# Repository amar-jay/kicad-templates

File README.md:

# KiCad Templates

> [!NOTE]
>	This is a fork of the original [KiCad Templates repository](https://gitlab.com/kicad/libraries/kicad-templates) to provide updated templates for KiCad 9.0 and later versions.
> This fork includes templates designed for specific manufacturers, usecases and inmproved aesthetics.
> It is personally maintained by [amar-jay](https://github.com/amar-jay). 

This repository contains the official KiCad project and worksheet templates.

Contribution guidelines can be found at http://kicad.org/libraries/contribute
The library convention can be found at http://kicad.org/libraries/klc/

Other KiCad library repositories are located:

* Symbols: https://gitlab.com/kicad/libraries/kicad-symbols
* Footprints: https://gitlab.com/kicad/libraries/kicad-footprints
* 3D Models: https://gitlab.com/kicad/libraries/kicad-packages3d

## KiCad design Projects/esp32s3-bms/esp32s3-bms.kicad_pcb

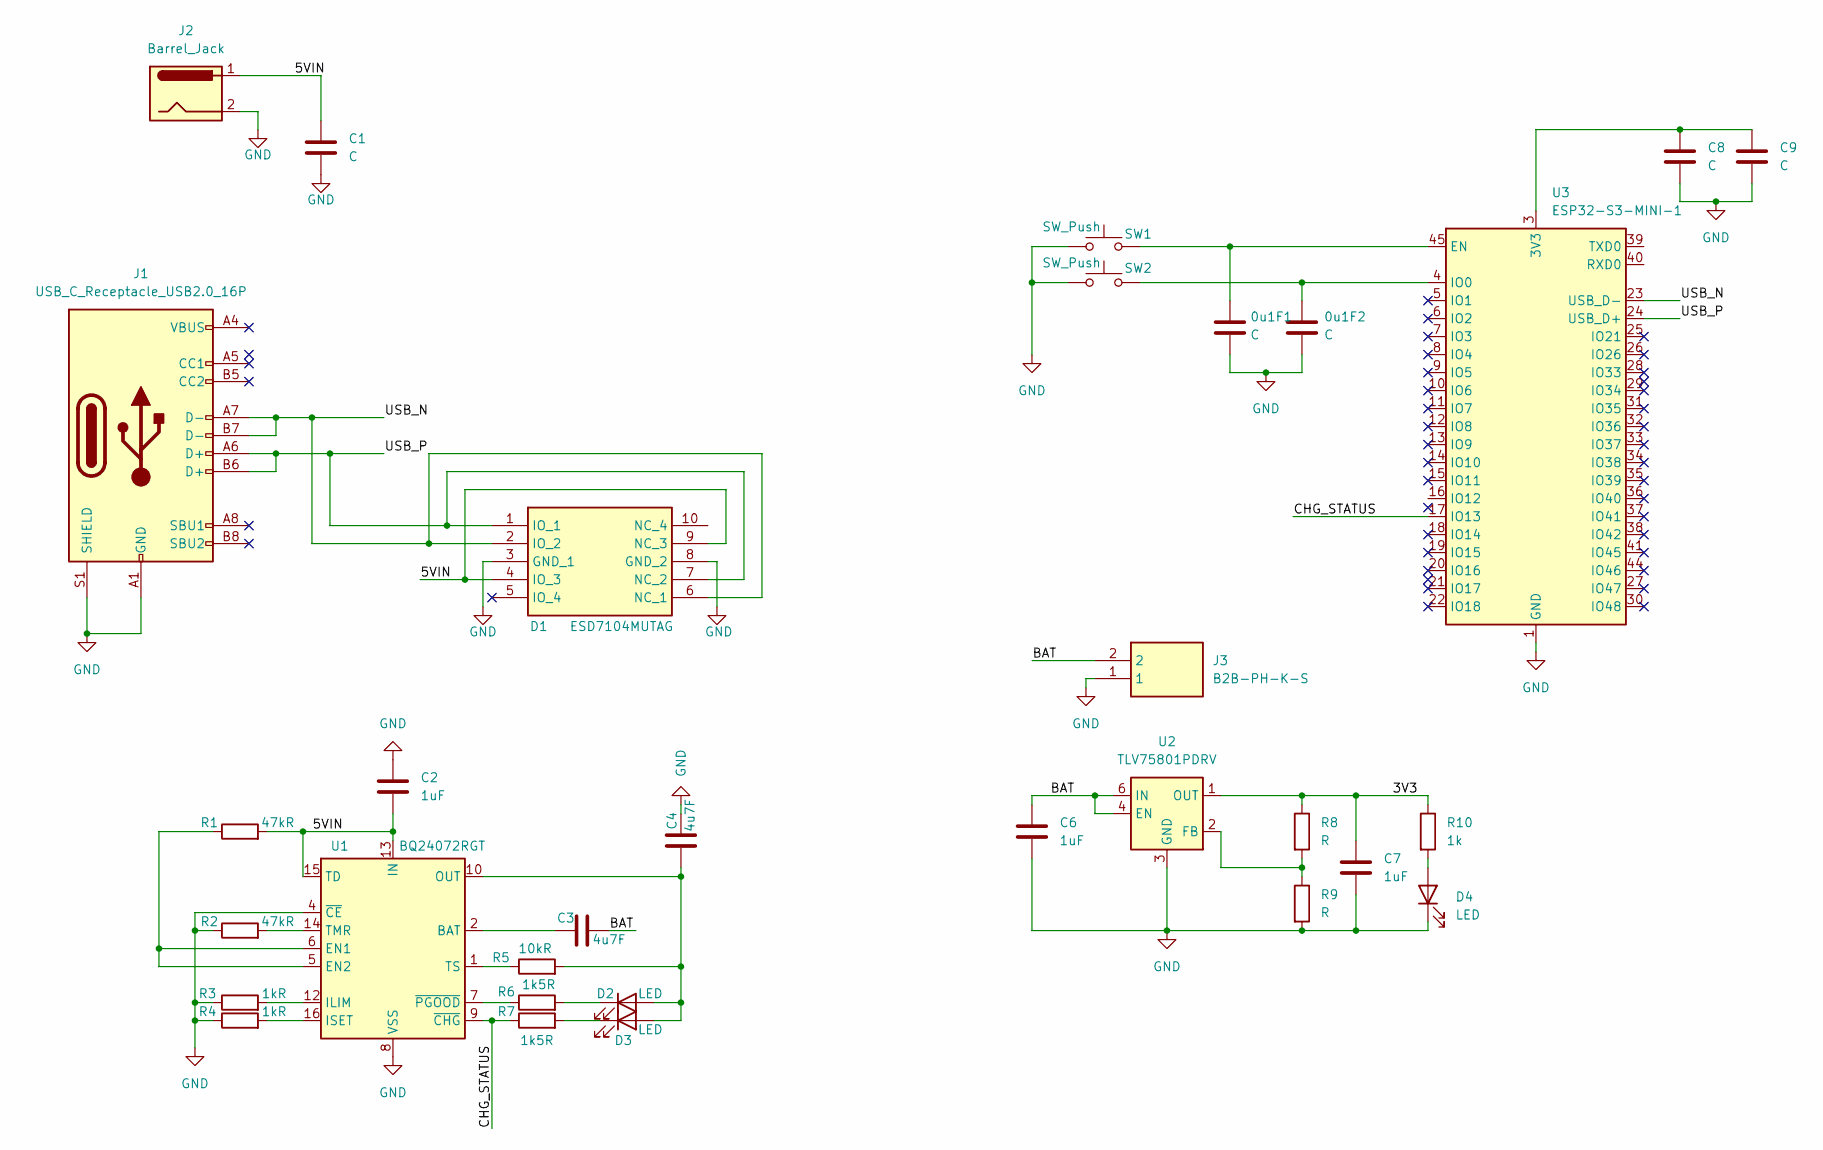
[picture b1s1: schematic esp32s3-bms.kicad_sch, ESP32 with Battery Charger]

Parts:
0u1F1, 0u1F2: C; C_0603_1608Metric
C1, C8, C9: C; C_0603_1608Metric
C2, C6, C7: 1uF; C_0603_1608Metric
C3, C4: 4u7F; C_0603_1608Metric
D1: ESD7104MUTAG; ESD8104MUTAG; Manufacturer_Part_Number ESD7104MUTAG; Mouser Part Number 863-ESD7104MUTAG
D2, D3, D4: LED; LED_0603_1608Metric
J1: USB_C_Receptacle_USB2.0_16P; USB_C_Receptacle_GCT_USB4105-xx-A_16P_TopMnt_Horizontal
J2: Barrel_Jack; BarrelJack_CUI_PJ-063AH_Horizontal
J3: B2B-PH-K-S; B2BPHKS; Manufacturer_Part_Number B2B-PH-K-S
R1, R2: 47kR; R_0201_0603Metric
R3, R4: 1kR; R_0201_0603Metric
R5: 10kR; R_0201_0603Metric
R6, R7: 1k5R; R_0201_0603Metric
R8, R9: R; R_0201_0603Metric
R10: 1k; R_0201_0603Metric
SW1, SW2: SW_Push; SW_SPST_PTS810
U1: BQ24072RGT; VQFN-16-1EP_3x3mm_P0.5mm_EP1.6x1.6mm
U2: TLV75801PDRV; WSON-6-1EP_2x2mm_P0.65mm_EP1x1.6mm
U3: ESP32-S3-MINI-1; ESP32-S2-MINI-1

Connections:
/3V3: C7.1, R8.1, R10.1, U2.1 (OUT)
/5VIN: C1.1, C2.2, D1.4 (IO_3), D1.9 (NC_3), J2.1, R1.2, U1.13 (IN), U1.15 (TD)
/BAT: C3.1, C6.1, J3.2, U2.4 (EN), U2.6 (IN)
/CHG_STATUS: R7.1, U1.9 (~CHG), U3.17 (IO13)
/USB_N: D1.2 (IO_2), D1.6 (NC_1), J1.A7 (D-), J1.B7 (D-), U3.23 (USB_D-)
/USB_P: D1.1 (IO_1), D1.7 (NC_2), J1.A6 (D+), J1.B6 (D+), U3.24 (USB_D+)
GND: 0u1F1.2, 0u1F2.2, C1.2, C2.1, C4.2, C6.2, C7.2, C8.2, C9.2, D1.3 (GND_1), D1.8 (GND_2), D4.1 (K), J1.A1 (GND), J1.A12 (GND), J1.B1 (GND), J1.B12 (GND), J1.S1 (SHIELD), J2.2, J3.1, R2.1, R3.1, R4.1, R9.2, SW1.1, SW2.1, U1.4 (~CE), U1.8 (VSS), U1.17 (VSS), U2.3 (GND), U2.7 (GND), U3.1 (GND), U3.2 (GND), U3.42 (GND), U3.43 (GND), U3.46 (GND), U3.47 (GND), U3.48 (GND), U3.49 (GND), U3.50 (GND), U3.51 (GND), U3.52 (GND), U3.53 (GND), U3.54 (GND), U3.55 (GND), U3.56 (GND), U3.57 (GND), U3.58 (GND), U3.59 (GND), U3.60 (GND), U3.61 (GND), U3.62 (GND), U3.63 (GND), U3.64 (GND), U3.65 (GND)
unnamed: C3.2, U1.2 (BAT), U1.3 (BAT)
unnamed: C4.1, D2.2 (A), D3.2 (A), R5.2, U1.10 (OUT), U1.11 (OUT)
unnamed: D2.1 (K), R6.2
unnamed: D3.1 (K), R7.2
unnamed: D4.2 (A), R10.2
unnamed: R1.1, U1.5 (EN2), U1.6 (EN1)
unnamed: R3.2, U1.12 (ILIM)
unnamed: R4.2, U1.16 (ISET)
unnamed: R2.2, U1.14 (TMR)
unnamed: R5.1, U1.1 (TS)
unnamed: R6.1, U1.7 (~PGOOD)
unnamed: R8.2, R9.1, U2.2 (FB)
unnamed: C8.1, C9.1, U3.3 (3V3)
unnamed: 0u1F1.1, SW1.2, U3.45 (EN)
unnamed: 0u1F2.1, SW2.2, U3.4 (IO0)

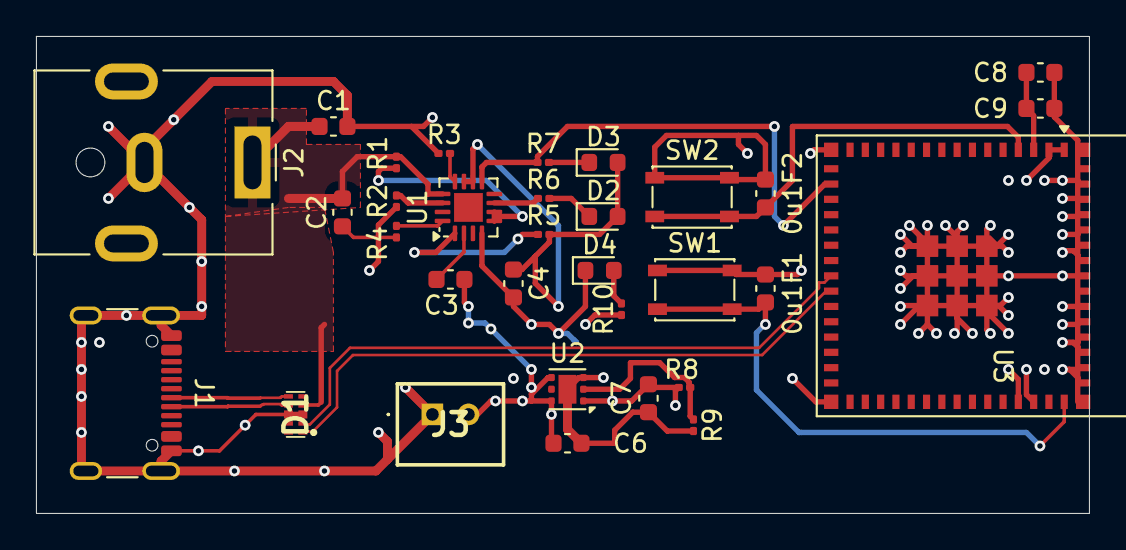
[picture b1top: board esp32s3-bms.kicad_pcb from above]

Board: 4 copper layers, 58.5 x 26.5 mm, 32 parts (0 on the bottom side), 22 nets.

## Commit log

2025-12-30 ESP32 with battery charger
2025-12-30 PCBWay Maufacturing template added
2025-12-30 JLCPCB 2 layer template
2025-12-30 JLCPCB Multilayer template
2025-12-30 Revise README for clarity and added link
    Updated README to include link to original repository and improved wording.
